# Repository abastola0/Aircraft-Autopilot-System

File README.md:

## Autopilot Enabled Data Sensing UAV

This repository presents the Autopilot System with features like Gyro Stabilization, Atmospheric data logging to sd card using dh11 and MQ9 sensors,Hovering on a defined area by setting rudder angle as per Transmitter potentiometer. 
  Thus full autopilot Control can be obtained by activating both stabilization and hovering feature to make the aircraft rotate above you within required area. Also, Gyrostabilization is featured with Sensitivity Control.

Also,plese checkout the video by clicking on the thumbnail below:

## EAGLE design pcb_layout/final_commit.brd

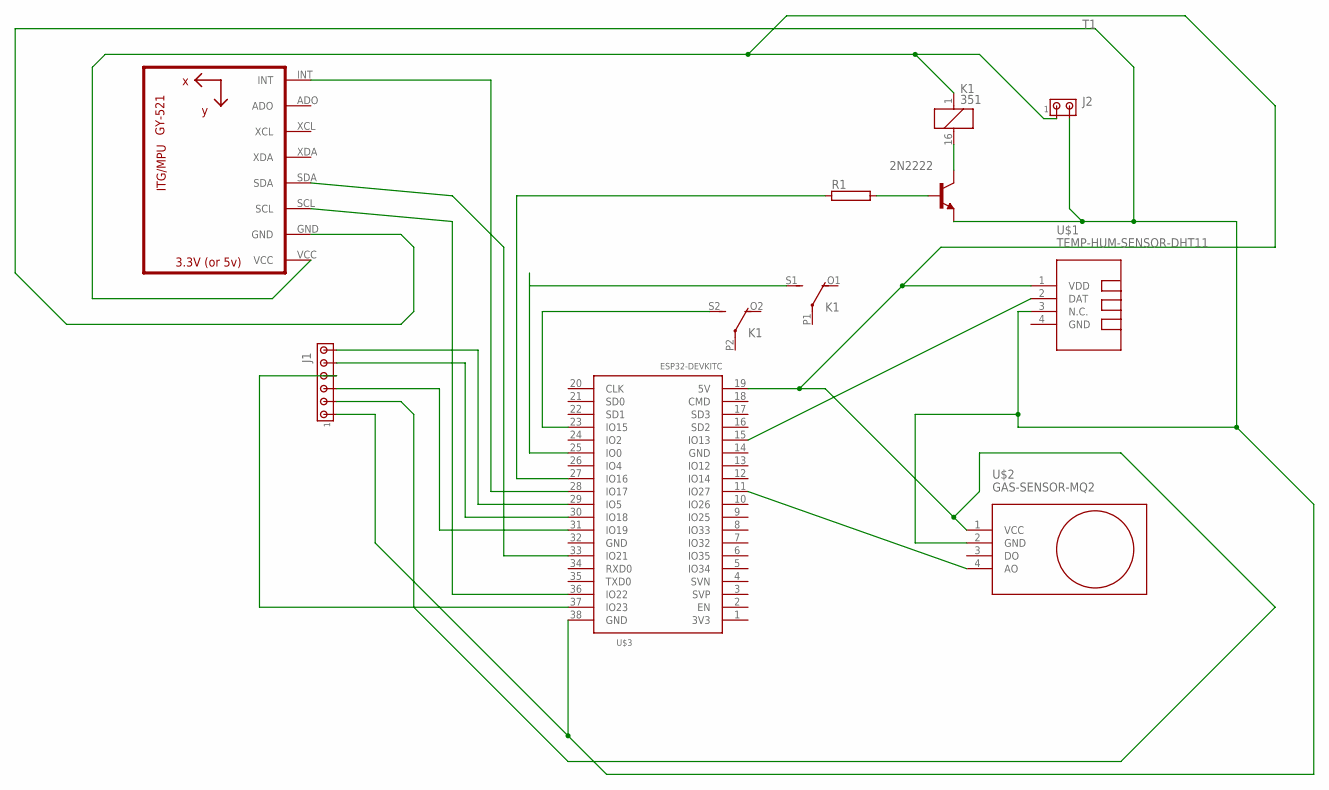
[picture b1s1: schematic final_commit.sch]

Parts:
J1: MTA06-100; 10X06MTA
J2: MTA02-100; 10X02MTA
K1: 351
R1: RMG100-V; TO-247-2V
T1: 2N2222; TO18
U2: GY-521MPU6050; GY-521
U$1: TEMP-HUM-SENSOR-DHT11
U$2: GAS-SENSOR-MQ2
U$3: ESP32DEVKITC; ESP32-DEVKITC

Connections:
GND: U$1.4 (GND)
unnamed: J1.6, U$3.29 (IO5)
unnamed: J1.5, U$3.30 (IO18)
unnamed: J1.4, U$3.37 (IO23)
unnamed: J1.3, U$3.31 (IO19)
unnamed: U2.INT, U$3.28 (IO17)
unnamed: U2.SCL, U$3.36 (IO22)
unnamed: U2.SDA, U$3.33 (IO21)
unnamed: U$1.2 (DAT), U$3.15 (IO13)
unnamed: U$2.4 (AO), U$3.11 (IO27)
unnamed: R1.2, T1.2 (B)
unnamed: R1.1, U$3.27 (IO16)
unnamed: K1.16 (2), T1.3 (C)
unnamed: K1.S1 (S), U$3.25 (IO0)
unnamed: K1.S2 (S), U$3.23 (IO15)
unnamed: J1.1, J2.2, T1.1 (E), U2.GND, U$1.3 (N.C.), U$2.2 (GND), U$3.38 (GND)
unnamed: J1.2, J2.1, K1.1, U2.VCC, U$1.1 (VDD), U$2.1 (VCC), U$3.19 (5V)

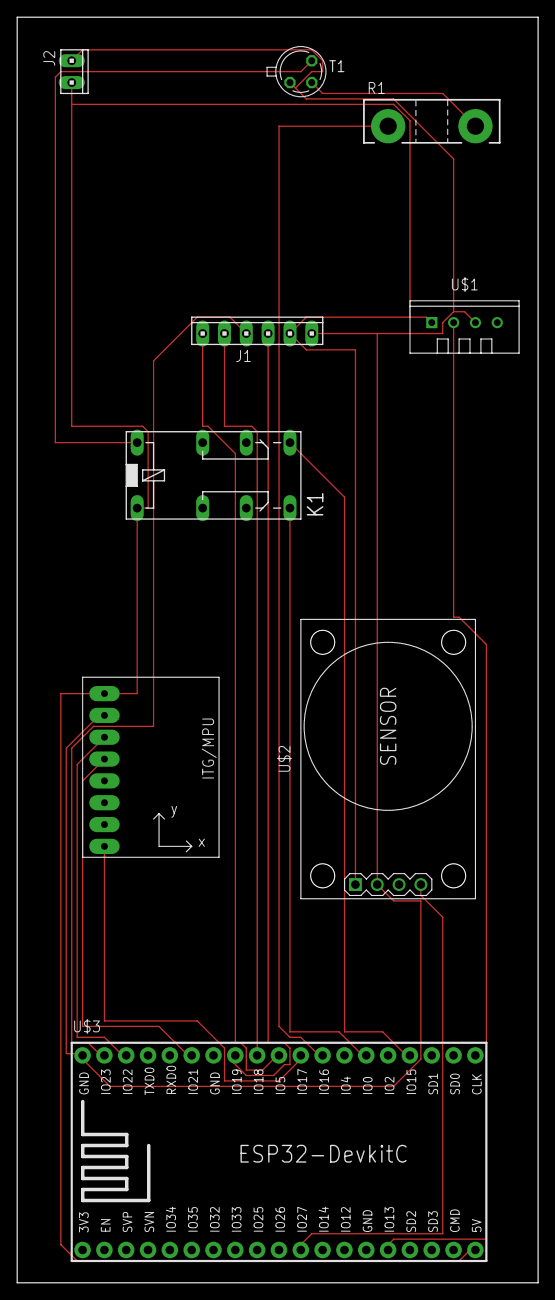
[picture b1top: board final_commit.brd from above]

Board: 2 copper layers, 60.6 x 147.3 mm, 9 parts (0 on the bottom side), 16 nets.

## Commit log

2019-07-10 added photos
2019-12-30 adding images
2019-12-30 image folder

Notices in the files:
parts and their libraries:
diy-modules: Released under the Creative Commons Attribution 4.0 International License: http://creativecommons.org/licenses/by/4.0
